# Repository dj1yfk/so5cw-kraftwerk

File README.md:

# SO5CW DC Power Distributor for Remote operation ("Kraftwerk")

by Fabian Kurz, DJ5CW/SO5CW <fabian@fkurz.net>

Homepage:   https://fkurz.net/ham/kraftwerk/

Repository: https://git.fkurz.net/dj1yfk/so5cw-kraftwerk/

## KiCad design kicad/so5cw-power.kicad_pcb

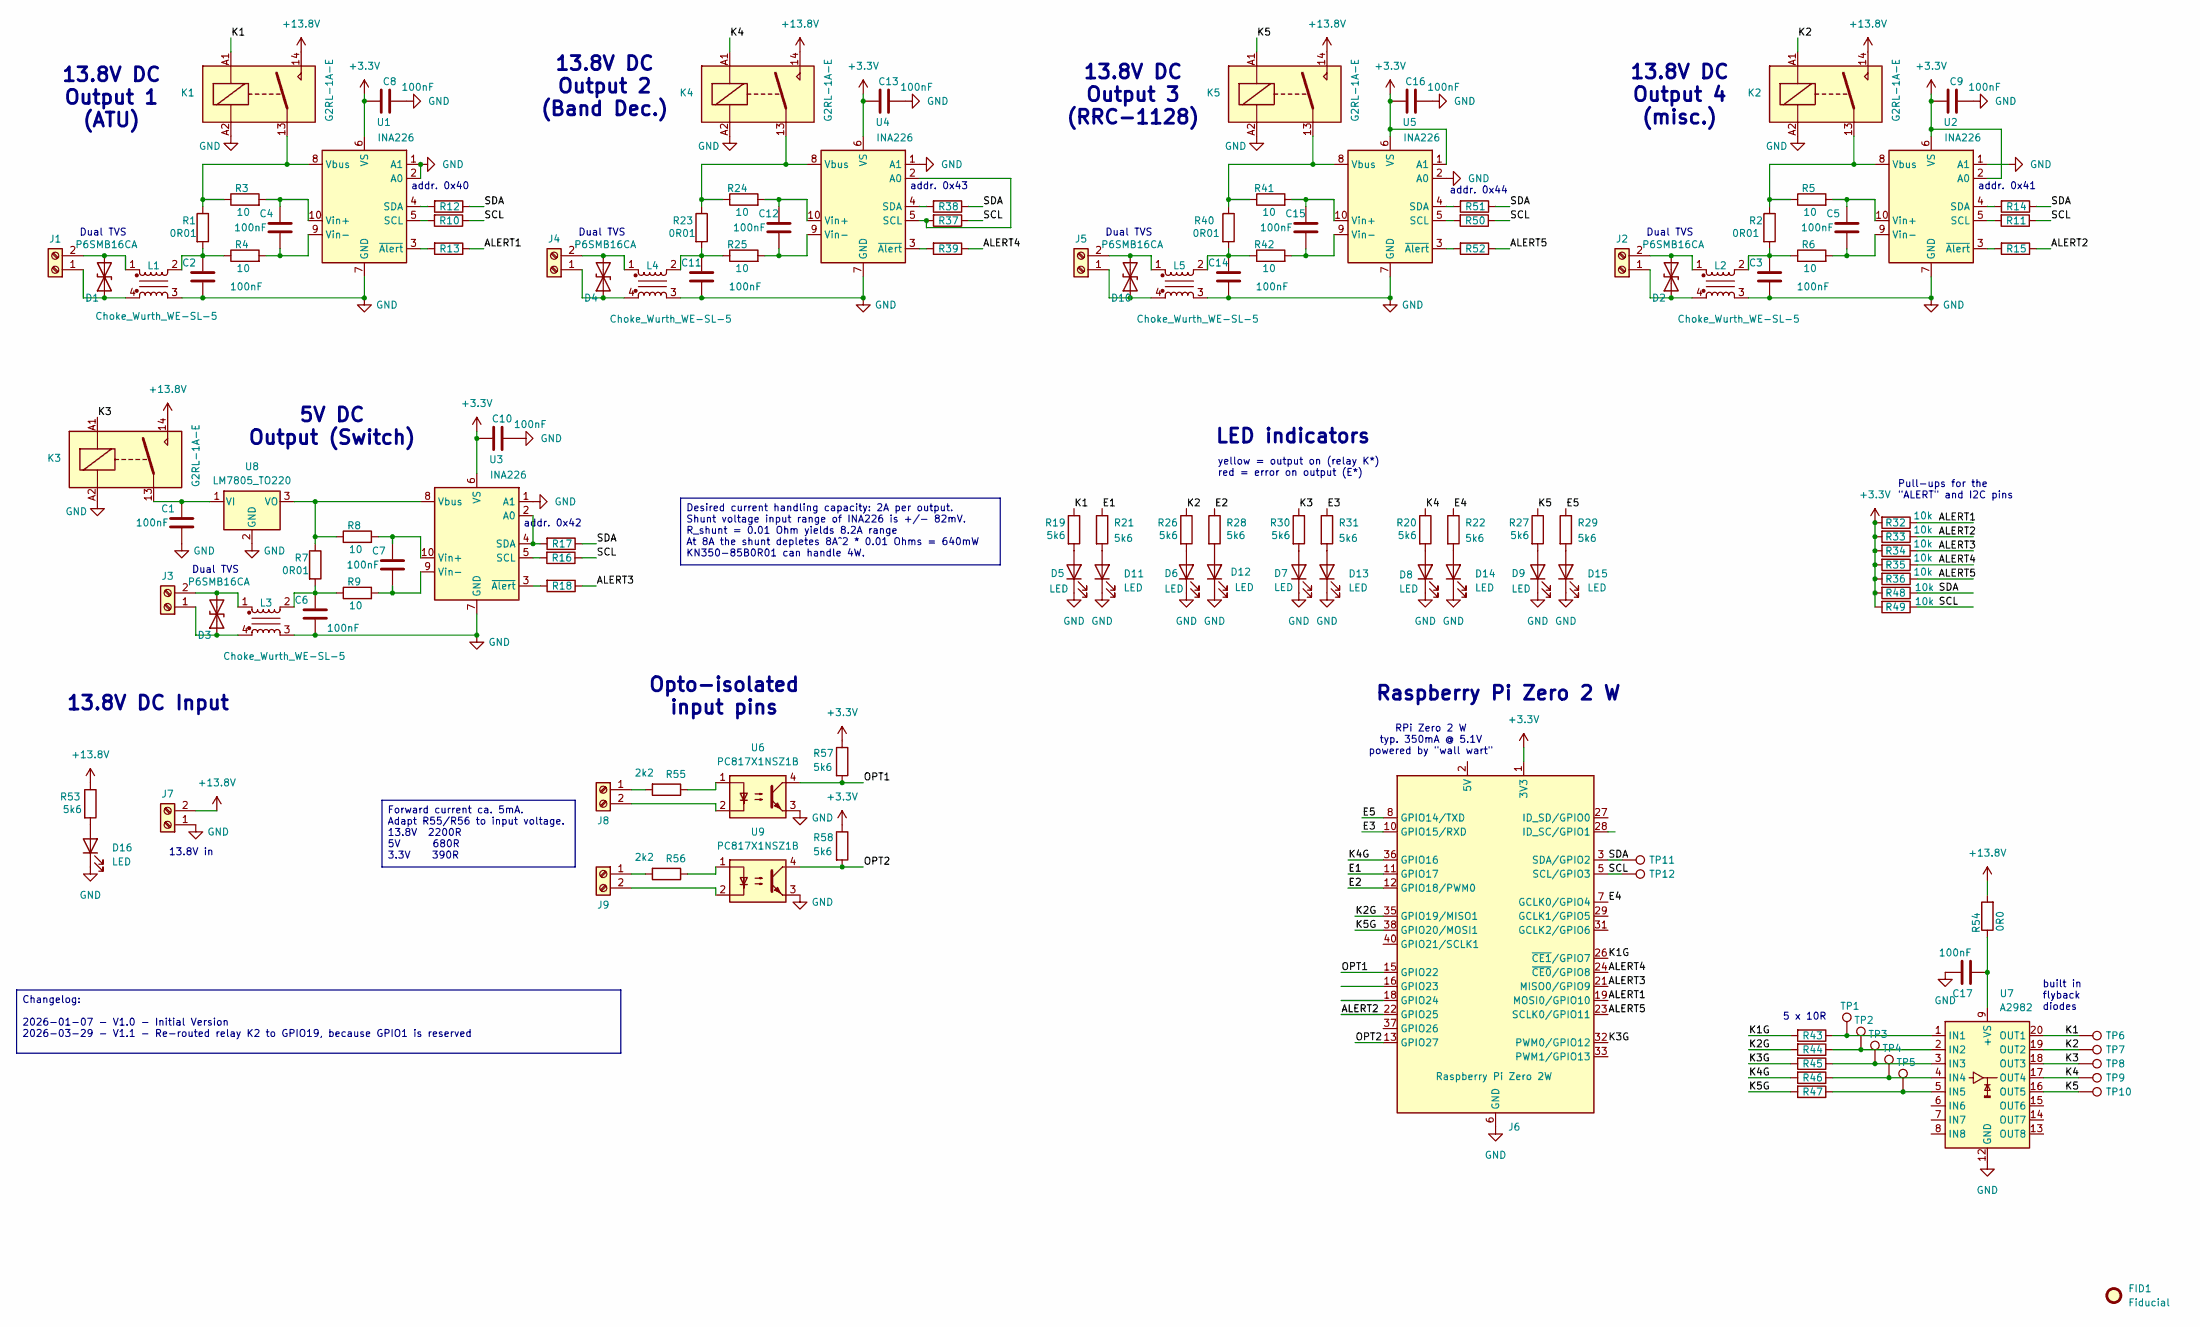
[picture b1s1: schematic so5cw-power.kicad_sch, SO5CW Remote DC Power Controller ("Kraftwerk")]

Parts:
C1, C2, C3, C4, C5, C6, C7, C8, C9, C10, C11, C12, C13, C14, C15, C16, C17: 100nF; C_0805_2012Metric_Pad1.18x1.45mm_HandSolder
D1, D2, D3, D4, D10: P6SMB16CA; D_SMB_Handsoldering
D5, D6, D7, D8, D9, D11, D12, D13, D14, D15, D16: LED; LED_0603_1608Metric_Pad1.05x0.95mm_HandSolder
FID1: Fiducial; bobik
J1, J2, J3, J4, J5, J7, J8, J9: Screw_Terminal_01x02; TerminalBlock_Phoenix_PT-1,5-2-3.5-H_1x02_P3.50mm_Horizontal
J6: Raspberry Pi Zero 2W; Raspberry Pi Zero W 2
K1, K2, K3, K4, K5: G2RL-1A-E; Relay_SPST_Omron_G2RL-1A-E
L1, L2, L3, L4, L5: Choke_Wurth_WE-SL-5; L_CommonModeChoke_Wuerth_WE-SL5
R1, R2, R7, R23, R40: 0R01; R_Axial_DIN0207_L6.3mm_D2.5mm_P5.08mm_Vertical
R3, R4, R5, R6, R8, R9, R24, R25, R41, R42, R43, R44, R45, R46, R47: 10; R_0603_1608Metric_Pad0.98x0.95mm_HandSolder
R10, R11, R12, R13, R14, R15, R16, R17, R18, R32, R33, R34, R35, R36, R37, R38, R39, R48, R49, R50, R51, R52: 10k; R_0603_1608Metric_Pad0.98x0.95mm_HandSolder
R19, R20, R21, R22, R26, R27, R28, R29, R30, R31, R53, R57, R58: 5k6; R_0603_1608Metric_Pad0.98x0.95mm_HandSolder
R54: 0R0; R_0603_1608Metric_Pad0.98x0.95mm_HandSolder
R55, R56: 2k2; R_0603_1608Metric_Pad0.98x0.95mm_HandSolder
TP1, TP2, TP3, TP4, TP5, TP6, TP7, TP8, TP9, TP10, TP11, TP12: TestPoint; TestPoint_THTPad_1.0x1.0mm_Drill0.5mm
U1, U2, U3, U4, U5: INA226; VSSOP-10_3x3mm_P0.5mm
U6, U9: PC817X1NSZ1B; DIP-4_W7.62mm_LongPads
U7: A2982; SOIC-20W_7.5x12.8mm_P1.27mm
U8: LM7805_TO220; TO-220-3_Vertical

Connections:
+3.3V: C8.1, C9.1, C10.1, C13.1, C16.1, J6.1 (3V3), J6.17 (3V3), R32.2, R33.2, R34.2, R35.2, R36.2, R48.2, R49.2, R57.1, R58.1, U1.6 (VS), U2.2 (A0), U2.6 (VS), U3.6 (VS), U4.6 (VS), U5.1 (A1), U5.6 (VS)
+13.8V: J7.2, K1.14, K2.14, K3.14, K4.14, K5.14, R53.1, R54.2
/ALERT1: J6.19 (MOSI0/GPIO10), R13.1, R32.1
/ALERT2: J6.22 (GPIO25), R15.1, R33.1
/ALERT3: J6.21 (MISO0/GPIO9), R18.1, R34.1
/ALERT4: J6.24 (~CE0/GPIO8), R35.1, R39.1
/ALERT5: J6.23 (SCLK0/GPIO11), R36.1, R52.1
/E1: J6.11 (GPIO17), R21.1
/E2: J6.12 (GPIO18/PWM0), R28.1
/E3: J6.10 (GPIO15/RXD), R31.1
/E4: J6.7 (GCLK0/GPIO4), R22.1
/E5: J6.8 (GPIO14/TXD), R29.1
/K1: K1.A1, R19.1, TP6.1, U7.20 (OUT1)
/K1G: J6.26 (~CE1/GPIO7), R43.2
/K2: K2.A1, R26.1, TP7.1, U7.19 (OUT2)
/K2G: J6.35 (GPIO19/MISO1), R44.2
/K3: K3.A1, R30.1, TP8.1, U7.18 (OUT3)
/K3G: J6.32 (PWM0/GPIO12), R45.2
/K4: K4.A1, R20.1, TP9.1, U7.17 (OUT4)
/K4G: J6.36 (GPIO16), R46.2
/K5: K5.A1, R27.1, TP10.1, U7.16 (OUT5)
/K5G: J6.38 (GPIO20/MOSI1), R47.2
/OPT1: J6.15 (GPIO22), R57.2, U6.4
/OPT2: J6.13 (GPIO27), R58.2, U9.4
/SCL: J6.5 (SCL/GPIO3), R10.1, R11.1, R16.1, R37.1, R49.1, R50.1, TP12.1
/SDA: J6.3 (SDA/GPIO2), R12.1, R14.1, R17.1, R38.1, R48.1, R51.1, TP11.1
GND: C1.2, C2.2, C3.2, C6.2, C8.2, C9.2, C10.2, C11.2, C13.2, C14.2, C16.2, C17.1, D5.1 (K), D6.1 (K), D7.1 (K), D8.1 (K), D9.1 (K), D11.1 (K), D12.1 (K), D13.1 (K), D14.1 (K), D15.1 (K), D16.1 (K), J6.6 (GND), J6.9 (GND), J6.14 (GND), J6.20 (GND), J6.25 (GND), J6.30 (GND), J6.34 (GND), J6.39 (GND), J7.1, K1.A2, K2.A2, K3.A2, K4.A2, K5.A2, L1.3, L2.3, L3.3, L4.3, L5.3, U1.1 (A1), U1.2 (A0), U1.7 (GND), U2.1 (A1), U2.7 (GND), U3.1 (A1), U3.7 (GND), U4.1 (A1), U4.7 (GND), U5.2 (A0), U5.7 (GND), U6.3, U7.12 (GND), U8.2 (GND), U9.3
unnamed: C2.1, L1.2, R1.2, R4.1
unnamed: C3.1, L2.2, R2.2, R6.1
unnamed: C6.1, L3.2, R7.2, R9.1
unnamed: C11.1, L4.2, R23.2, R25.1
unnamed: C14.1, L5.2, R40.2, R42.1
unnamed: D1.1 (A1), J1.1, L1.4
unnamed: D1.2 (A2), J1.2, L1.1
unnamed: D2.1 (A1), J2.1, L2.4
unnamed: D2.2 (A2), J2.2, L2.1
unnamed: D3.1 (A1), J3.1, L3.4
unnamed: D3.2 (A2), J3.2, L3.1
unnamed: D4.1 (A1), J4.1, L4.4
unnamed: D4.2 (A2), J4.2, L4.1
unnamed: D5.2 (A), R19.2
unnamed: D6.2 (A), R26.2
unnamed: D7.2 (A), R30.2
unnamed: D8.2 (A), R20.2
unnamed: D9.2 (A), R27.2
unnamed: D10.1 (A1), J5.1, L5.4
unnamed: D10.2 (A2), J5.2, L5.1
unnamed: D11.2 (A), R21.2
unnamed: D12.2 (A), R28.2
unnamed: D13.2 (A), R31.2
unnamed: D14.2 (A), R22.2
unnamed: D15.2 (A), R29.2
unnamed: D16.2 (A), R53.2
unnamed: J6.2 (5V), J6.4 (5V)
unnamed: J8.1, R55.2
unnamed: J8.2, U6.2
unnamed: J9.1, R56.2
unnamed: J9.2, U9.2
unnamed: R55.1, U6.1
unnamed: R56.1, U9.1
unnamed: R10.2, U1.5 (SCL)
unnamed: R12.2, U1.4 (SDA)
unnamed: K1.13, R1.1, R3.1, U1.8 (Vbus)
unnamed: C4.1, R3.2, U1.10 (Vin+)
unnamed: C4.2, R4.2, U1.9 (Vin-)
unnamed: R13.2, U1.3 (~Alert)
unnamed: R11.2, U2.5 (SCL)
unnamed: R14.2, U2.4 (SDA)
unnamed: K2.13, R2.1, R5.1, U2.8 (Vbus)
unnamed: C5.1, R5.2, U2.10 (Vin+)
unnamed: C5.2, R6.2, U2.9 (Vin-)
unnamed: R15.2, U2.3 (~Alert)
unnamed: R17.2, U3.2 (A0), U3.4 (SDA)
unnamed: R16.2, U3.5 (SCL)
unnamed: R7.1, R8.1, U3.8 (Vbus), U8.3 (VO)
unnamed: C7.1, R8.2, U3.10 (Vin+)
unnamed: C7.2, R9.2, U3.9 (Vin-)
unnamed: R18.2, U3.3 (~Alert)
unnamed: R37.2, U4.2 (A0), U4.5 (SCL)
unnamed: R38.2, U4.4 (SDA)
unnamed: K4.13, R23.1, R24.1, U4.8 (Vbus)
unnamed: C12.1, R24.2, U4.10 (Vin+)
unnamed: C12.2, R25.2, U4.9 (Vin-)
unnamed: R39.2, U4.3 (~Alert)
unnamed: R50.2, U5.5 (SCL)
unnamed: R51.2, U5.4 (SDA)
unnamed: K5.13, R40.1, R41.1, U5.8 (Vbus)
unnamed: C15.1, R41.2, U5.10 (Vin+)
unnamed: C15.2, R42.2, U5.9 (Vin-)
unnamed: R52.2, U5.3 (~Alert)
unnamed: C17.2, R54.1, U7.9 (+VS)
unnamed: R43.1, TP1.1, U7.1 (IN1)
unnamed: R44.1, TP2.1, U7.2 (IN2)
unnamed: R45.1, TP3.1, U7.3 (IN3)
unnamed: R46.1, TP4.1, U7.4 (IN4)
unnamed: R47.1, TP5.1, U7.5 (IN5)
unnamed: C1.1, K3.13, U8.1 (VI)

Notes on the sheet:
13.8V DC Output 2 (Band Dec.)
addr. 0x41
Pull-ups for the "ALERT" and I2C pins
Dual TVS
built in flyback diodes
5V DC Output (Switch)
addr. 0x40
13.8V in
13.8V DC Input
addr. 0x44
addr. 0x43
Opto-isolated input pins
13.8V DC Output 4 (misc.)
addr. 0x42
RPi Zero 2 W typ. 350mA @ 5.1V powered by "wall wart"
Raspberry Pi Zero 2 W
5 x 10R
LED indicators
13.8V DC Output 1 (ATU)
13.8V DC Output 3 (RRC-1128)
yellow = output on (relay K*) red = error on output (E*)
Desired current handling capacity: 2A per output. Shunt voltage input range of INA226 is +/- 82mV. R_shunt = 0.01 Ohm yields 8.2A range At 8A the shunt depletes 8A^2 * 0.01 Ohms = 640mW KN350-85B0R01 can handle 4W.
Changelog: 2026-01-07 - V1.0 - Initial Version 2026-03-29 - V1.1 - Re-routed relay K2 to GPIO19, because GPIO1 is reserved
Forward current ca. 5mA. Adapt R55/R56 to input voltage. 13.8V 2200R 5V 680R 3.3V 390R

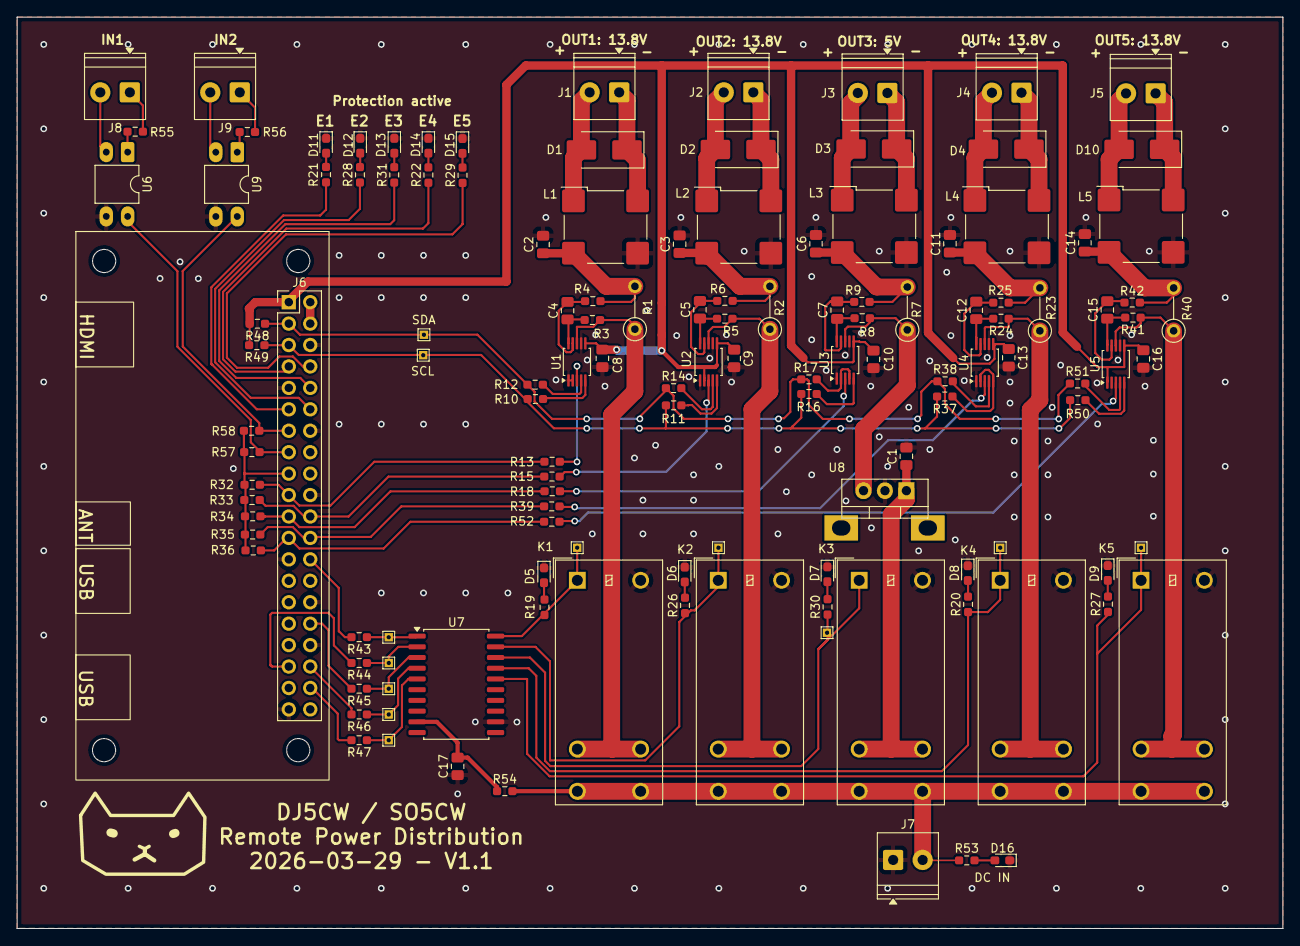
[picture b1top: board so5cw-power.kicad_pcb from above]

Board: 2 copper layers, 149.9 x 107.9 mm, 132 parts (0 on the bottom side), 97 nets.

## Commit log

2026-03-15 Initial commit. WIP - Software for SO5CW remote power switch
2026-03-15 add "fuse" functions, syslog output
2026-03-22 add PCB v1.0
2026-03-22 README.md cosmetics
2026-03-22 add measured voltage to alert message
2026-03-22 FW: read current a 2nd time before blowing the fuse
    In long term tests, there were occasional I2C read errors that lead
    to switching off a channel that did not have an overload condition.
    Therefore, if we detect an overcurrent, read the current twice, and
    only if that second reading is also above the limit, switch off.
    The 2nd read occurs within a millisecond of the first one, so there
    is little danger that anything goes up in smoke in the meantime.
2026-03-24 Connect Relay K2 to GPIO19, because GPIO1 is reserved
2026-03-29 Version 1.1 (K2 re-routed from GPIO1 to GPIO19). Cosmetics.
2026-03-29 Add history of opto coupler input pins. Rename channels to physical name (1-5).
2026-03-29 schematic: rearrange outputs (1..5) and adjust descriptions
2026-03-29 README.txt reformatted
